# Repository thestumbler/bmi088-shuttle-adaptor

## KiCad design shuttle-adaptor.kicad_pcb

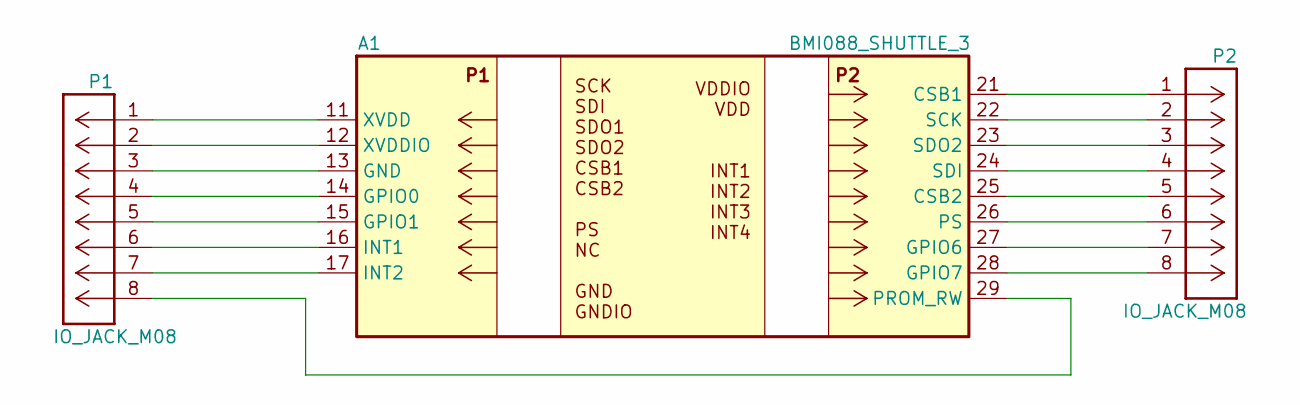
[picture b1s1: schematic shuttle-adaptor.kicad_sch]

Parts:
A1: BMI088_SHUTTLE_3; ASSY_BMI088_SHUTTLE_3
P1, P2: IO_JACK_M08; PinHeader_1x08_P2.54mm_Vertical

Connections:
unnamed: A1.21 (CSB1), P2.1
unnamed: A1.25 (CSB2), P2.5
unnamed: A1.13 (GND), P1.3
unnamed: A1.14 (GPIO0), P1.4
unnamed: A1.15 (GPIO1), P1.5
unnamed: A1.27 (GPIO6), P2.7
unnamed: A1.28 (GPIO7), P2.8
unnamed: A1.16 (INT1), P1.6
unnamed: A1.17 (INT2), P1.7
unnamed: A1.29 (PROM_RW), P1.8
unnamed: A1.26 (PS), P2.6
unnamed: A1.22 (SCK), P2.2
unnamed: A1.24 (SDI), P2.4
unnamed: A1.23 (SDO2), P2.3
unnamed: A1.11 (XVDD), P1.1
unnamed: A1.12 (XVDDIO), P1.2

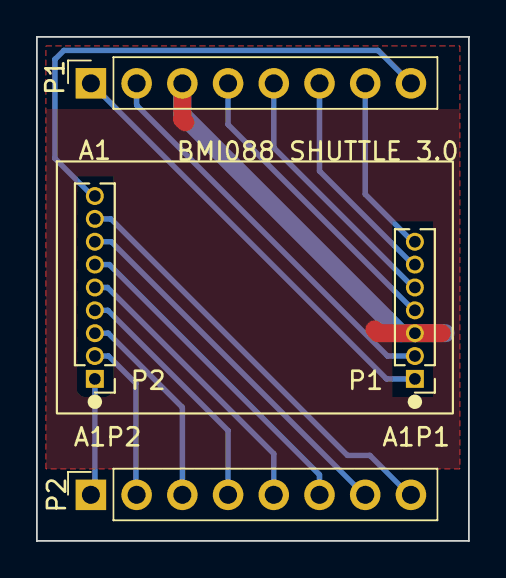
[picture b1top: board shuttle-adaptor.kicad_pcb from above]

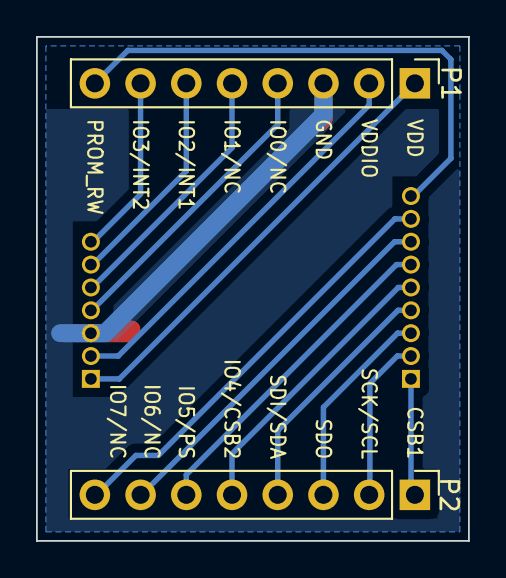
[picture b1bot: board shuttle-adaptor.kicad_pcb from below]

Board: 2 copper layers, 24.0 x 28.0 mm, 3 parts (2 on the bottom side), 16 nets.

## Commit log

2023-11-11 added images and gerber zip
